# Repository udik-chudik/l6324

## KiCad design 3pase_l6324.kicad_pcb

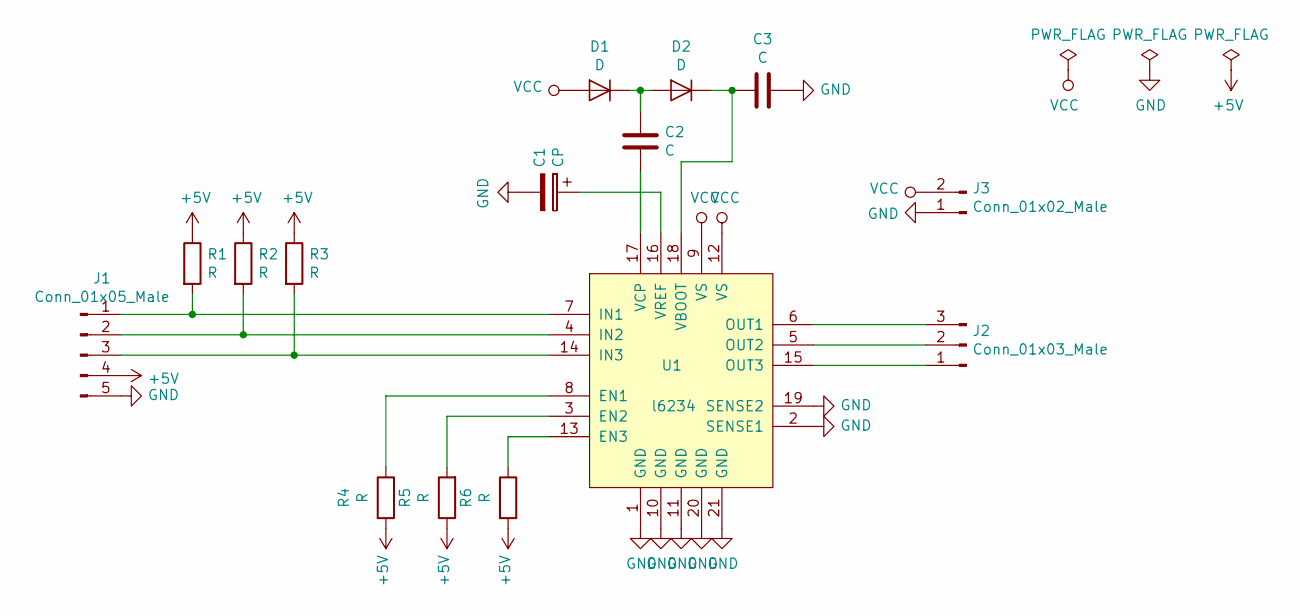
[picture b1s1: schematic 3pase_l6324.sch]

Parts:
C1: CP; C_0603_1608Metric
C2, C3: C; C_0603_1608Metric
D1, D2: D; D_1206_3216Metric
J1: Conn_01x05_Male; PinHeader_1x05_P2.54mm_Vertical
J2: Conn_01x03_Male; PinHeader_1x03_P2.54mm_Vertical
J3: Conn_01x02_Male; PinHeader_1x02_P2.54mm_Vertical
R1, R2, R3, R4, R5, R6: R; R_0603_1608Metric
U1: l6234; so20

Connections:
+5V: J1.4, R1.1, R2.1, R3.1, R4.2, R5.1, R6.2
GND: C1.2, C3.1, J1.5, J3.1, U1.1 (GND), U1.2 (SENSE1), U1.10 (GND), U1.11 (GND), U1.19 (SENSE2), U1.20 (GND), U1.21 (GND)
unnamed: C1.1, U1.16 (VREF)
unnamed: C2.1, U1.17 (VCP)
unnamed: C2.2, D1.1 (K), D2.2 (A)
unnamed: C3.2, D2.1 (K), U1.18 (VBOOT)
unnamed: J1.1, R1.2, U1.7 (IN1)
unnamed: J1.2, R2.2, U1.4 (IN2)
unnamed: J1.3, R3.2, U1.14 (IN3)
unnamed: J2.1, U1.15 (OUT3)
unnamed: J2.2, U1.5 (OUT2)
unnamed: J2.3, U1.6 (OUT1)
unnamed: R4.1, U1.8 (EN1)
unnamed: R5.2, U1.3 (EN2)
unnamed: R6.1, U1.13 (EN3)
VCC: D1.2 (A), J3.2, U1.9 (VS), U1.12 (VS)

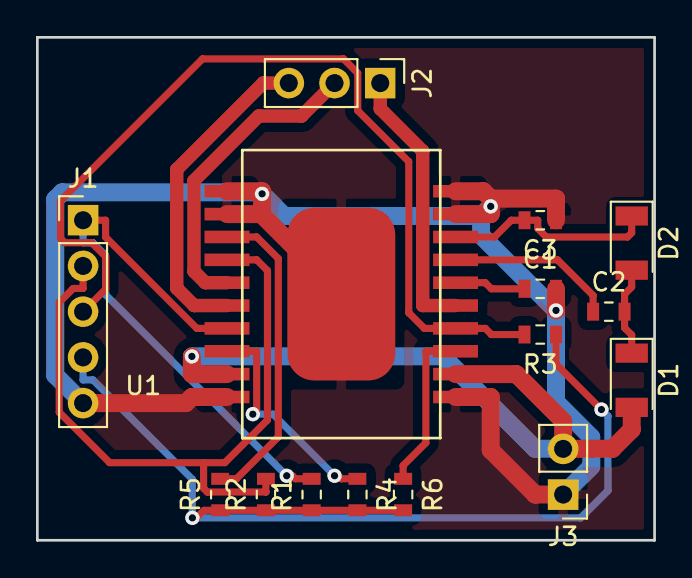
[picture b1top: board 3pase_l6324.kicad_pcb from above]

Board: 2 copper layers, 34.3 x 27.9 mm, 15 parts (0 on the bottom side), 16 nets.
